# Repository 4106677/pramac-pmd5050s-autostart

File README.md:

# Pramac PMD5050S — автозапуск на ESP32 (ESPHome)

Заміна штатного блоку автозапуску (ATS) для дизель-генератора **Pramac PMD5050S** (двигун 186FA, 50 Гц ≈ 3000 об/хв): плата-носій на KiCad + прошивка ESPHome + картка Home Assistant.

> ⚠️ Це реальний генератор зі стартером і мережева напруга 230 В на виході контактора. Безпека важливіша за швидкість. Проєкт особистий, без гарантій; використовуєте на свій ризик.

| Плата, верх | Плата, низ | Home Assistant |
|---|---|---|
|  |  |  |

## Що вміє
- **Автозапуск** по сухому контакту REMOTE (інвертор/ATS) або перемикачу «Запуск з HA»: подає ACC, крутить стартер до появи обертів (до 3 спроб), тримає ACC, поки запит активний.
- **Контактор з прогрівом:** після запуску чекає **40 с**, потім замикає реле K3 (сухі COM/NO під котушку контактора 230 В). На **СТОП** спершу розмикає K3, двигун ще **20 с** працює без навантаження, потім знімається ACC. Несподівана зупинка двигуна одразу розмикає K3. Час задається `warmup_s`, `cooldown_s`.
- **Оберти** з сигналу TAHO (допоміжна обмотка маховика) через LM393: ~18 300 імп/хв ≈ 3 050 об/хв при 6 імп/оберт. Поріг «двигун працює» 1000 об/хв.
- **Моточаси** (`duty_time`, зберігаються у флеші, старт з нуля), логування обертів лише коли вони ≠ 0.
- **Безпечні стани:** після перезавантаження плати всі реле вимкнені (NPN-драйвер з підтяжкою бази до GND), запит з HA скидається, двигун сам не стартує.

## Плата v5.1 (KiCad 10, 93,2 × 82 мм, 2 шари)
Файли в [`hardware/`](hardware/):

| Файл | Призначення |
|---|---|
| `pramac_carrier.kicad_pcb` | плата (відкривається в KiCad PCB Editor) |
| `pramac_carrier_gerbers.zip` | Gerber + drill для виробника |
| `fit_check_1to1.pdf` | креслення 1:1, роздрукувати без масштабу й приміряти ESP32 та клеми |
| `BOM.md` | повний список компонентів |
| `pramac_carrier.kicad_dru` | правило зазору 2,5 мм для мережевих ланцюгів контактора |
| `generate_board.py`, `qr.txt` | генератор плати через `pcbnew` |

### Що змінилось у v5.1
- **RM20S-050:** на v5 контур корпусу на шовкографії був намальований не з того боку, тому модуль легко поставити задом наперед. Розводка виводів не змінилась (1 +VIN, 2 GND, 3 +VOUT), але тепер контур стоїть з боку D2, а біля виводів підписано **IN / GND / OUT**. На платі v5 модуль ставиться так само: корпусом до D2.
- **Іоністор SC1** (JEC 1 Ф 5,5 В, овал 16 × 8 × 14 мм) має власне посадкове місце з кроком 11,8 мм між ESP32 і реле K1/K2. Тепер він стоїть прямо на платі, без друкованої підставки.
- Щоб звільнити місце, ESP32 піднято на 2 мм, а шину +12 В до реле опущено й звужено до 4 мм.
- D1 і D2 зсунуто ліворуч, щоб звільнити місце під корпус RM20S. D3 перенесено під кріпильний отвір H1, F1 стоїть під D3, QR-код на звороті трохи нижче.

### Клеми (DG128-5.0, всі з одного боку)
`BATT−  BATT+` | `CHG+  CHG−` (зарядний паралельно входу, до запобіжника) | `ACC  START` (виходи реле NO, +12 В) | `CONTACTOR` (сухі COM/NO реле K3, 230 В) | `TAHO  REMOTE` (REMOTE — два контакти сухого контакту).

### Живлення і реле
- Запобіжник T 2 А (радіальний KLS5-102-5RT-020H) → TVS → 1N5821 → C1/C2 (2× 4700 мкФ) → DC-DC Favotek RM20S-050 (5 В 2 А) → 1N5821 → вузол 5 В (+ іоністор SC1).
- Реле: 3× SRD-05VDC-SL-A. K1 (ACC), K2 (START): COM до +12 В шиною 4 мм, NO на клему доріжкою 4 мм (≈10 А при 2 oz). Шина +12 В йде **до** запобіжника, тому на проводі від АКБ потрібен окремий зовнішній запобіжник (~15 А).
- Драйвер кожного реле: BC337 + резистор бази 1 кОм + підтяжка бази 10 кОм до GND + діод 1N4148 на котушці.

### ESP32
DevKit V1 30-pin **лежить горизонтально** (антена ліворуч, USB праворуч), вставляється в прямі гнізда 1×15 (відстань між рядами 25,4 мм). Під антеною немає міді, під модулем стоять лише низькі деталі.

| Пін | Призначення |
|---|---|
| D14 | TAHO (вихід LM393 → `pulse_counter`) |
| D25 | REMOTE, `INPUT_PULLUP`, замкнуто = GND (через R6 1 кОм, фільтр C6) |
| D2 / D4 / D26 | реле ACC / START / контактор (активний HIGH) |
| D27, D13 | резервний роз'єм J3 (не використовується в прошивці) |

### Вхід TAHO
Taho → R1 22 кОм → два стабілітрони BZX55C5V1 зустрічно на GND → C3 10 мкФ (неполярний) → LM393 IN−; зсув 1,65 В дільником 10 кОм/10 кОм, гістерезис R4 100 кОм, pull-up R5 4,7 кОм на 3V3. Живий дріт Taho **не можна** садити на масу.

### Нижній бік
QR на цей репозиторій, логотип GitHub і нік.

## Прошивка
```bash
cd esphome
cp secrets.yaml.example secrets.yaml   # заповніть своїми значеннями
esphome config pramac-pmd5050s.yaml
esphome compile pramac-pmd5050s.yaml
```
ESPHome 2025.4.1. Константи: `pulses_per_rev`, `running_rpm_threshold`, `warmup_s`, `cooldown_s` у `substitutions`. Для цієї плати реле мають `inverted: false`.

## Home Assistant
Картка зі шкалою обертів і перемикачем: [`homeassistant/generator-card.yaml`](homeassistant/generator-card.yaml) (замініть entity_id на свої; для перемикача «Запуск з HA» варто увімкнути підтвердження натискання).

## Корпус для друку (ABS)
Основа + кришка + червона вставка з логотипом Pramac (без гвинтів, на клею), додаткові опори й напрямні для плати, кріплення на стіну вушками, кришка на M3 з латунними вставками. Параметрична модель: [`enclosure/`](enclosure/) (STL, скрипт для Fusion, генератор на Python, інструкція).

## Замовлення плати
Для PCBWay: 2 шари, 1,6 мм, мідь **2 oz** (шина 10 А), HASL без свинцю, файл `pramac_carrier_gerbers.zip`. Майже всі компоненти виводні (THT), тож плату зручно паяти вручну; готові модулі (ESP32 DevKit, RM20S) ставляться як є.

## Порядок першого запуску
1. Роздрукувати `fit_check_1to1.pdf` 1:1, приміряти ESP32, колодки, клеми (відстань між рядами, висота під модулем ~8,5 мм).
2. Зібрати плату без ESP32, перевірити 5 В і 3,3 В, TVS/запобіжник.
3. Прошити, перевірити, що **всі три реле вимкнені** при подачі живлення й після кількох перезавантажень.
4. Перевірити TAHO на працюючому двигуні (~3 050 об/хв), звірити `pulses_per_rev` (частота на виході × 60).
5. Дріт **START до генератора підключати останнім**.
6. Контактор перевірити окремо без навантаження (прогрів 40 с, СТОП: K3 розмикається, через 20 с знімається ACC).

## Жорсткі правила
- START підключати останнім, після перевірки, що реле вимкнені під час завантаження.
- Не додавати логіку, яка вмикає START, коли двигун міг уже крутитися.
- Знятий ACC = двигун глухне; реле ACC вимикається при перезавантаженні плати (свідомий компроміс).
- Захист TAHO не послаблювати без обговорення.
- Мережеві (230 В) ланцюги контактора перевіряти окремо: плата не сертифікована.

## Відкрите
- Звірити `pulses_per_rev` по частоті на виході генератора.
- Не перевірено на залізі: відстань між рядами ESP32, розпіновка D-підписів вашого DevKit, розпіновка клемників (за datasheet), зазори мережевого ланцюга.
- Brownout під час старту Wi-Fi: перевірити 5 В на VIN ESP32.
- Схеми `.kicad_sch` немає: плата зібрана з нетлисту в скрипті.
- Рівень пального: пізніше.

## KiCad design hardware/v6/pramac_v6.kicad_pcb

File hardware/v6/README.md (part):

# Плата v6.1

**v6.1 (14.11.2026): переробка входу TAHO.** Перевірено на платі 5.1 з тією самою схемою входу:
у v6.0 резистор R31 тягнув вхід LM393 до опорної напруги VB, і в спокої компаратор стояв на порозі та ловив шум
(оберти росли до 20 000 на заглушеному двигуні). Тепер:
- **R31 10k** іде з TAHO_AC на GND: у спокої вхід на 0 В, нижче порогу, вихід LM393 HIGH.
- **Поріг VB:** R32 22k / R33 10k + гістерезис R34 100k дають 0,97 / 1,18 В (на 5.1 після переробки виміряно 1,2 В).
- **Фільтр R38 10k / C33 10 нФ** (100 мкс) перед LM393 гасить короткі (3–25 мкс) голки від регулятора зарядки генератора.
- **BAV99 (D25)** обмежує вхід LM393 від −0,6 до ~3,9 В.

Решта плати без змін: розводку v6.0 збережено, заново розведені тільки ланцюги TAHO_AC, TAHO_F і VB
(`patch_v61.py prep <плата v6.0>` → Freerouting → `patch_v61.py finish` → `gen_pcb.py export`).
DRC: 0 помилок, 0 незведених, 3 попередження про шовкографію (ті самі, що у v6.0).
Прошивка для v6 ще не написана; рахувати оберти треба так само, як `esphome/taho_rpm.h` (полярність входу та сама, що на переробленій 5.1).

Плата під заводську збірку JLCPCB (PCBA): майже все SMD, решту (реле, клеми, модуль AC-DC, мережевий запобіжник, варистор) завод теж паяє, сервісом THT. Допаювати нічого не треба.

| Файл | Що це |
|---|---|
| `pramac_v6_schematic.pdf` | схема для перегляду |
| `pramac_v6.kicad_sch`, `pramac_v6.kicad_pro`, `pramac_v6.kicad_sym`, `sym-lib-table` | проєкт KiCad 10 (схема + власні символи CN3767 і AO4421) |
| `pramac_v6_bom.csv` | BOM у форматі JLCPCB (Comment, Designator, Footprint, LCSC) |
| `gen_schematic.py`, `charger.py`, `parts.py`, `kisch.py` | генератор схеми: `python3 gen_schematic.py` |
| `pramac_v6.kicad_pcb`, `pramac_v6.kicad_dru` | плата 125 × 100 мм, 2 шари, і правило зазору 2,5 мм для 230 В |
| `pramac_v6_gerbers.zip` | гербери + свердління для JLCPCB |
| `pramac_v6_bom.csv`, `pramac_v6_cpl.csv` | BOM і файл розміщення (CPL) для заводської збірки |
| `pcb-top.png`, `pcb-bottom.png`, `drc.rpt` | рендери і звіт DRC |
| `gen_pcb.py`, `pramac_v6.dsn`, `pramac_v6.ses` | генератор плати: `gen_pcb.py place` → Freerouting (`.dsn` → `.ses`) → `gen_pcb.py route` → `gen_pcb.py export` |

## Що змінилось порівняно з v5.1
- **ESP32-S3-MINI-1U-N8** розпаяний на платі (15,4 × 15,4 мм), роз'єм U.FL під зовнішню антену: кабель U.FL → SMA на стінці корпусу. Прошивка й лог по USB-C (USB вбудований у чип), кнопки BOOT і RESET.
- **Живлення без іоністора:** два маленькі перетворювачі прямо від АКБ. AP63203 дає 3,3 В для ESP32 і працює від 3,8 В. AP63205 дає окремі 5 В для котушок реле. Обидва мають режим LDO: коли АКБ під час прокрутки падає нижче 5 В, вихід 5 В іде слідом за входом, а реле SRD-05 тримаються аж до ~2 В на котушці. Тому **іоністор більше не потрібен**.
- **Реле** ті самі Songle SRD-05VDC-SL-C. Ключі AO3400A, діоди на котушках, світлодіод стану на кожному реле.
- **Четверте реле K4 AUX** для підігрівача перед пуском або соленоїда декомпресії. COM на шині АКБ, як у ACC і START, вихід на окремий клемник J8 (AUX, GND).
- **Зарядка АКБ від 230 В:** модуль Mean Well IRM-20-24 → зарядник CN3767. Заряд 14,8 В, підтримка 13,55 В (задані всередині мікросхеми), струм 1 А. Підходить для звичайних свинцевих і AGM.
- **Детектор мережі:** оптопара LTV-814 на вході 230 В.
- **DIP-перемикач на 4 позиції** для вибору режиму, **4 кріплення M3 по кутах**, знімні клемники 5,08 мм.

## Живлення
`BATTERY+` → самовідновлюваний запобіжник 2 А (PTC) → `VBF` (TVS SMBJ18A, вихід зарядника, вимір напруги АКБ) → SS54 → `VIN12` (470 мкФ).
Від `VIN12` живляться AP63203 (3,3 В, ESP32) і AP63205 (`V5`, тільки котушки реле й світлодіоди реле).
Від USB: `VBUS` → SS34 → `VIN12`, тобто ESP32 можна прошити без 12 В.
Шина `VBAT` (до запобіжника) іде на COM реле ACC і START. На дроті від АКБ, як і раніше, потрібен зовнішній запобіжник ~15 А.

## Зарядник
- **Живлення і перемикач:** `V24` з модуля через P-MOSFET Q20. Ним керує ESP32 (`CHG_EN`): HIGH, або коли ESP32 не працює, зарядка йде; LOW — вимкнена. Прошивка вимикає зарядку на час прокрутки стартера і коли DIP2 вимкнений.
- **Струм:** 0,12 В / R66 = 1 А при R66 = 0,12 Ом. Модуль на 20 Вт має запас: зарядник бере близько 17 Вт.
- **Захист модуля від перевантаження:** дільник MPPT (150k/10k). Якщо модуль просяде нижче ~19 В, зарядник сам зменшить струм.
- **Стан:** `CHG_STAT` (заряджається) і `CHG_DONE` (заряджено) йдуть на ESP32 і на два світлодіоди.

## Піни ESP32-S3
| GPIO | Сигнал | GPIO | Сигнал |
|---|---|---|---|
| IO1 | напруга АКБ (АЦП, дільник 100k/22k) | IO9 | світлодіод STATUS |
| IO2 | CHG_DONE | IO10 / IO11 / IO12 | реле K1 ACC / K2 START / K3 контактор |
| | | IO21 | реле K4 AUX |
| IO4 | TAHO (LM393) | IO13–IO16 | DIP1–DIP4 |
| IO5 | REMOTE (сухий контакт між двома клемами REMOTE) | IO17, IO18 | резервна гребінка J7 |
| IO6 | MAINS_OK (мережа є = LOW) | IO19 / IO20 | USB D− / D+ |
| IO7 | CHG_EN | IO0 / EN | BOOT / RESET |
| IO8 | CHG_STAT | | |

## DIP-перемикач
1. Режим: OFF — запуск за сигналом REMOTE; ON — запуск, коли пропала мережа.
2. Зарядка дозволена.
3. Затримка запуску: 10 с або 60 с.
4. AUX: OFF — K4 працює як підігрів (вмикається на N секунд до прокрутки), ON — як декомпресія (тримається під час прокрутки).

## Роз'єми (знімні клемники 5,08 мм)
| Роз'єм | Контакти |
|---|---|
| J1 | AC IN: L, N |
| J2 | CONTACTOR: COM, NO (сухі контакти, 230 В) |
| J3 | BATTERY: +, − |
| J4 | ACC, START |
| J5 | TAHO; REMOTE, REMOTE (два контакти під сухий контакт або кнопку, полярність не важлива) |
| J8 | AUX: вихід K4 (+12 В з АКБ), GND |

Плагіни до клемників (WJ2EDGK, 5 × 2P і 1 × 3P) JLCPCB надсилає разом із замовленням окремими деталями.

**Навантаження на AUX.** Контакт реле SRD розрахований на 10 А. Свічки розжарювання і соленоїд декомпресії в момент втягування часто беруть більше. Тому для них ставте зовнішнє автомобільне реле на 30–40 А: його котушку підключити до J8 (AUX і GND), а силові контакти — напряму від АКБ через свій запобіжник. Слабке навантаження до ~8 А можна живити від J8 напряму.

## Плата
- **Розмір і кріплення:** 125 × 100 мм, 2 шари, 4 отвори M3 по кутах (за 4 мм від країв).
- **Зона 230 В ліворуч:** модуль AC-DC, запобіжник, варистор, реле контактора K3, детектор мережі (три резистори й оптопара під модулем AC-DC), клемники AC IN і CONTACTOR. Полігону землі там немає. Правило DRC тримає ≥ 2,5 мм від будь-якої мережевої міді до низьковольтної. Оптопара й модуль AC-DC стоять на межі зон.
- **Реле K4, K1, K2** стоять в один ряд на місці, що звільнилось у нижньому лівому куті. Їхні COM з'єднує одна шина АКБ.
- **Сильнострумові ланцюги** розведені вручну по нижньому шару. Шина АКБ від J3 до COM реле і виходи ACC/START/AUX мають ширину 3–4 мм.
- **Решта** розведена Freerouting. Земля: полігони з обох боків, перехідні отвори біля кожного SMD-виводу GND і зшивання сіткою 5 мм.
- **DRC:** 0 помилок, усі зв'язки з'єднані. Лишилось 3 попередження про шовкографію; на виводах завод її сам обрізає.
- **Розташування:** ESP32 угорі праворуч (роз'єм U.FL для кабелю до SMA на корпусі), USB-C на правому краю, кнопки RESET/BOOT під модулем, клемники вздовж нижнього краю.

## Замовлення на JLCPCB
- **PCB:** 2 шари, 1,6 мм, мідь **2 oz** (струм реле до 10 А), HASL без свинцю, файл `pramac_v6_gerbers.zip`.
- **Збірка:** у PCB Assembly завантажити `pramac_v6_bom.csv` і `pramac_v6_cpl.csv`. Виводні деталі (реле, клемники, IRM-20-24, запобіжник, варистор) завод теж паяє, сервісом THT.
- **Обов'язково перегляньте в превʼю JLCPCB поворот деталей:** у бібліотеки JLC своя орієнтація, і частину кутів (SOT-23, діоди, модуль ESP32, USB-C) зазвичай доводиться підправити там же.
- **Звірте посадкові місця на етапі DFM JLCPCB.** Їх я взяв з бібліотеки KiCad, вони відповідають корпусам у даташитах, але завод це перевіряє окремо:
  - клемники WJ2EDGRC (посадкове місце Phoenix MSTBA 5,08);
  - оптопара LTV-814S (SMDIP-4);
  - DIP-перемикач.
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
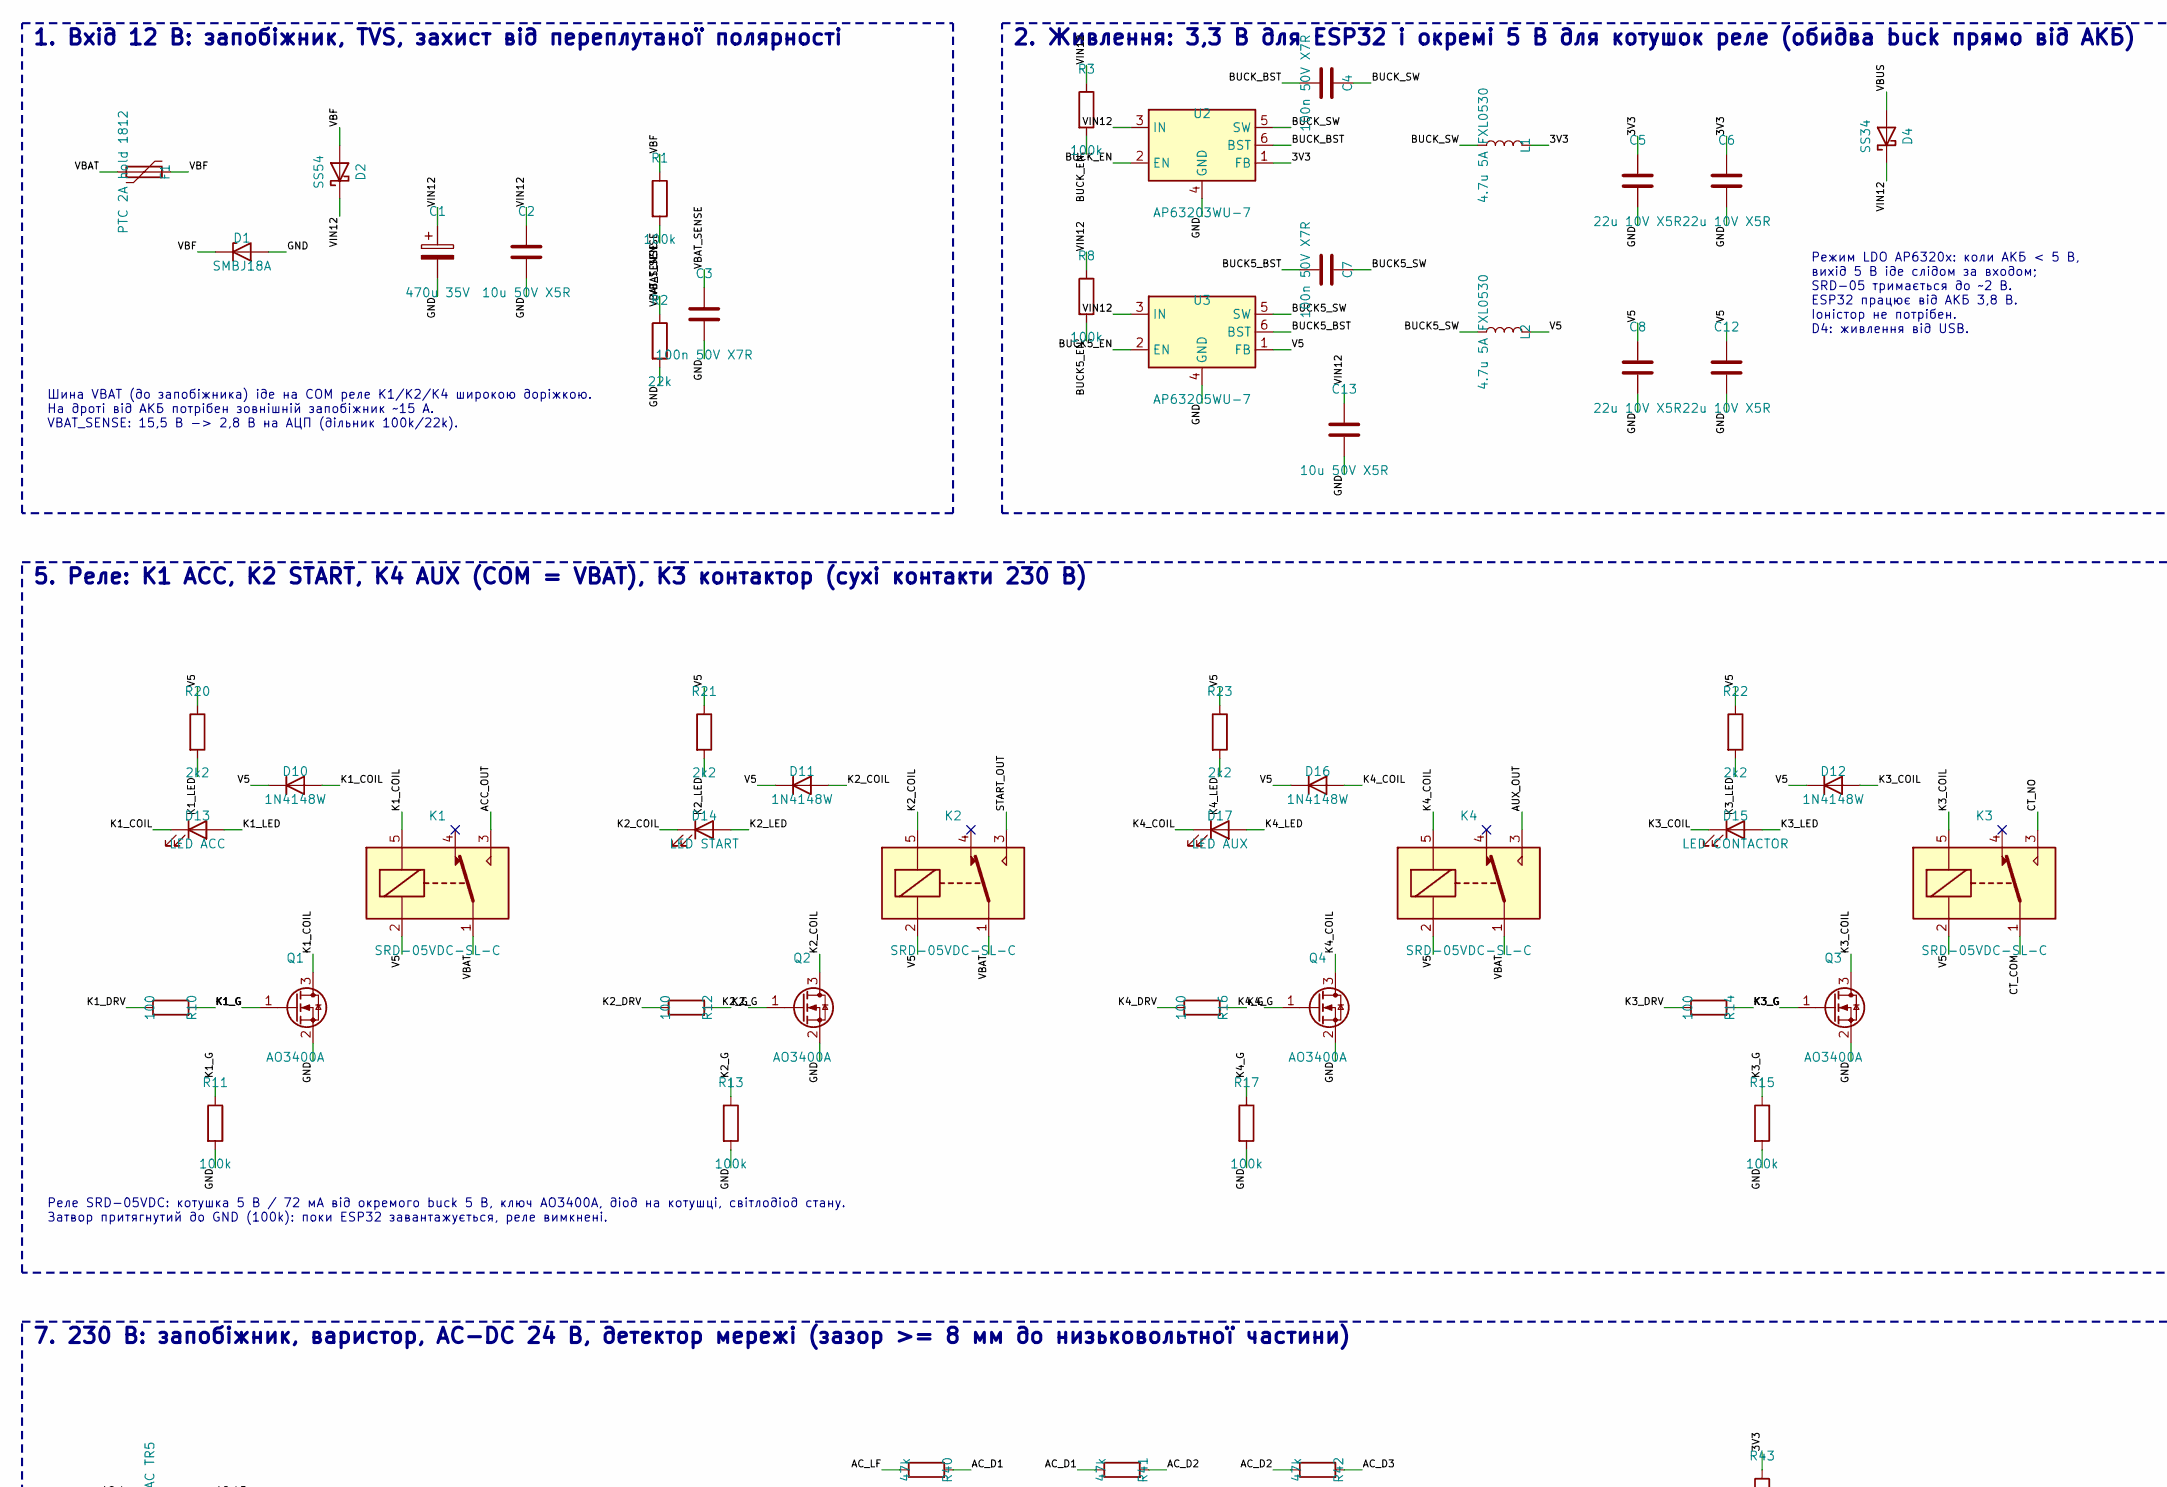
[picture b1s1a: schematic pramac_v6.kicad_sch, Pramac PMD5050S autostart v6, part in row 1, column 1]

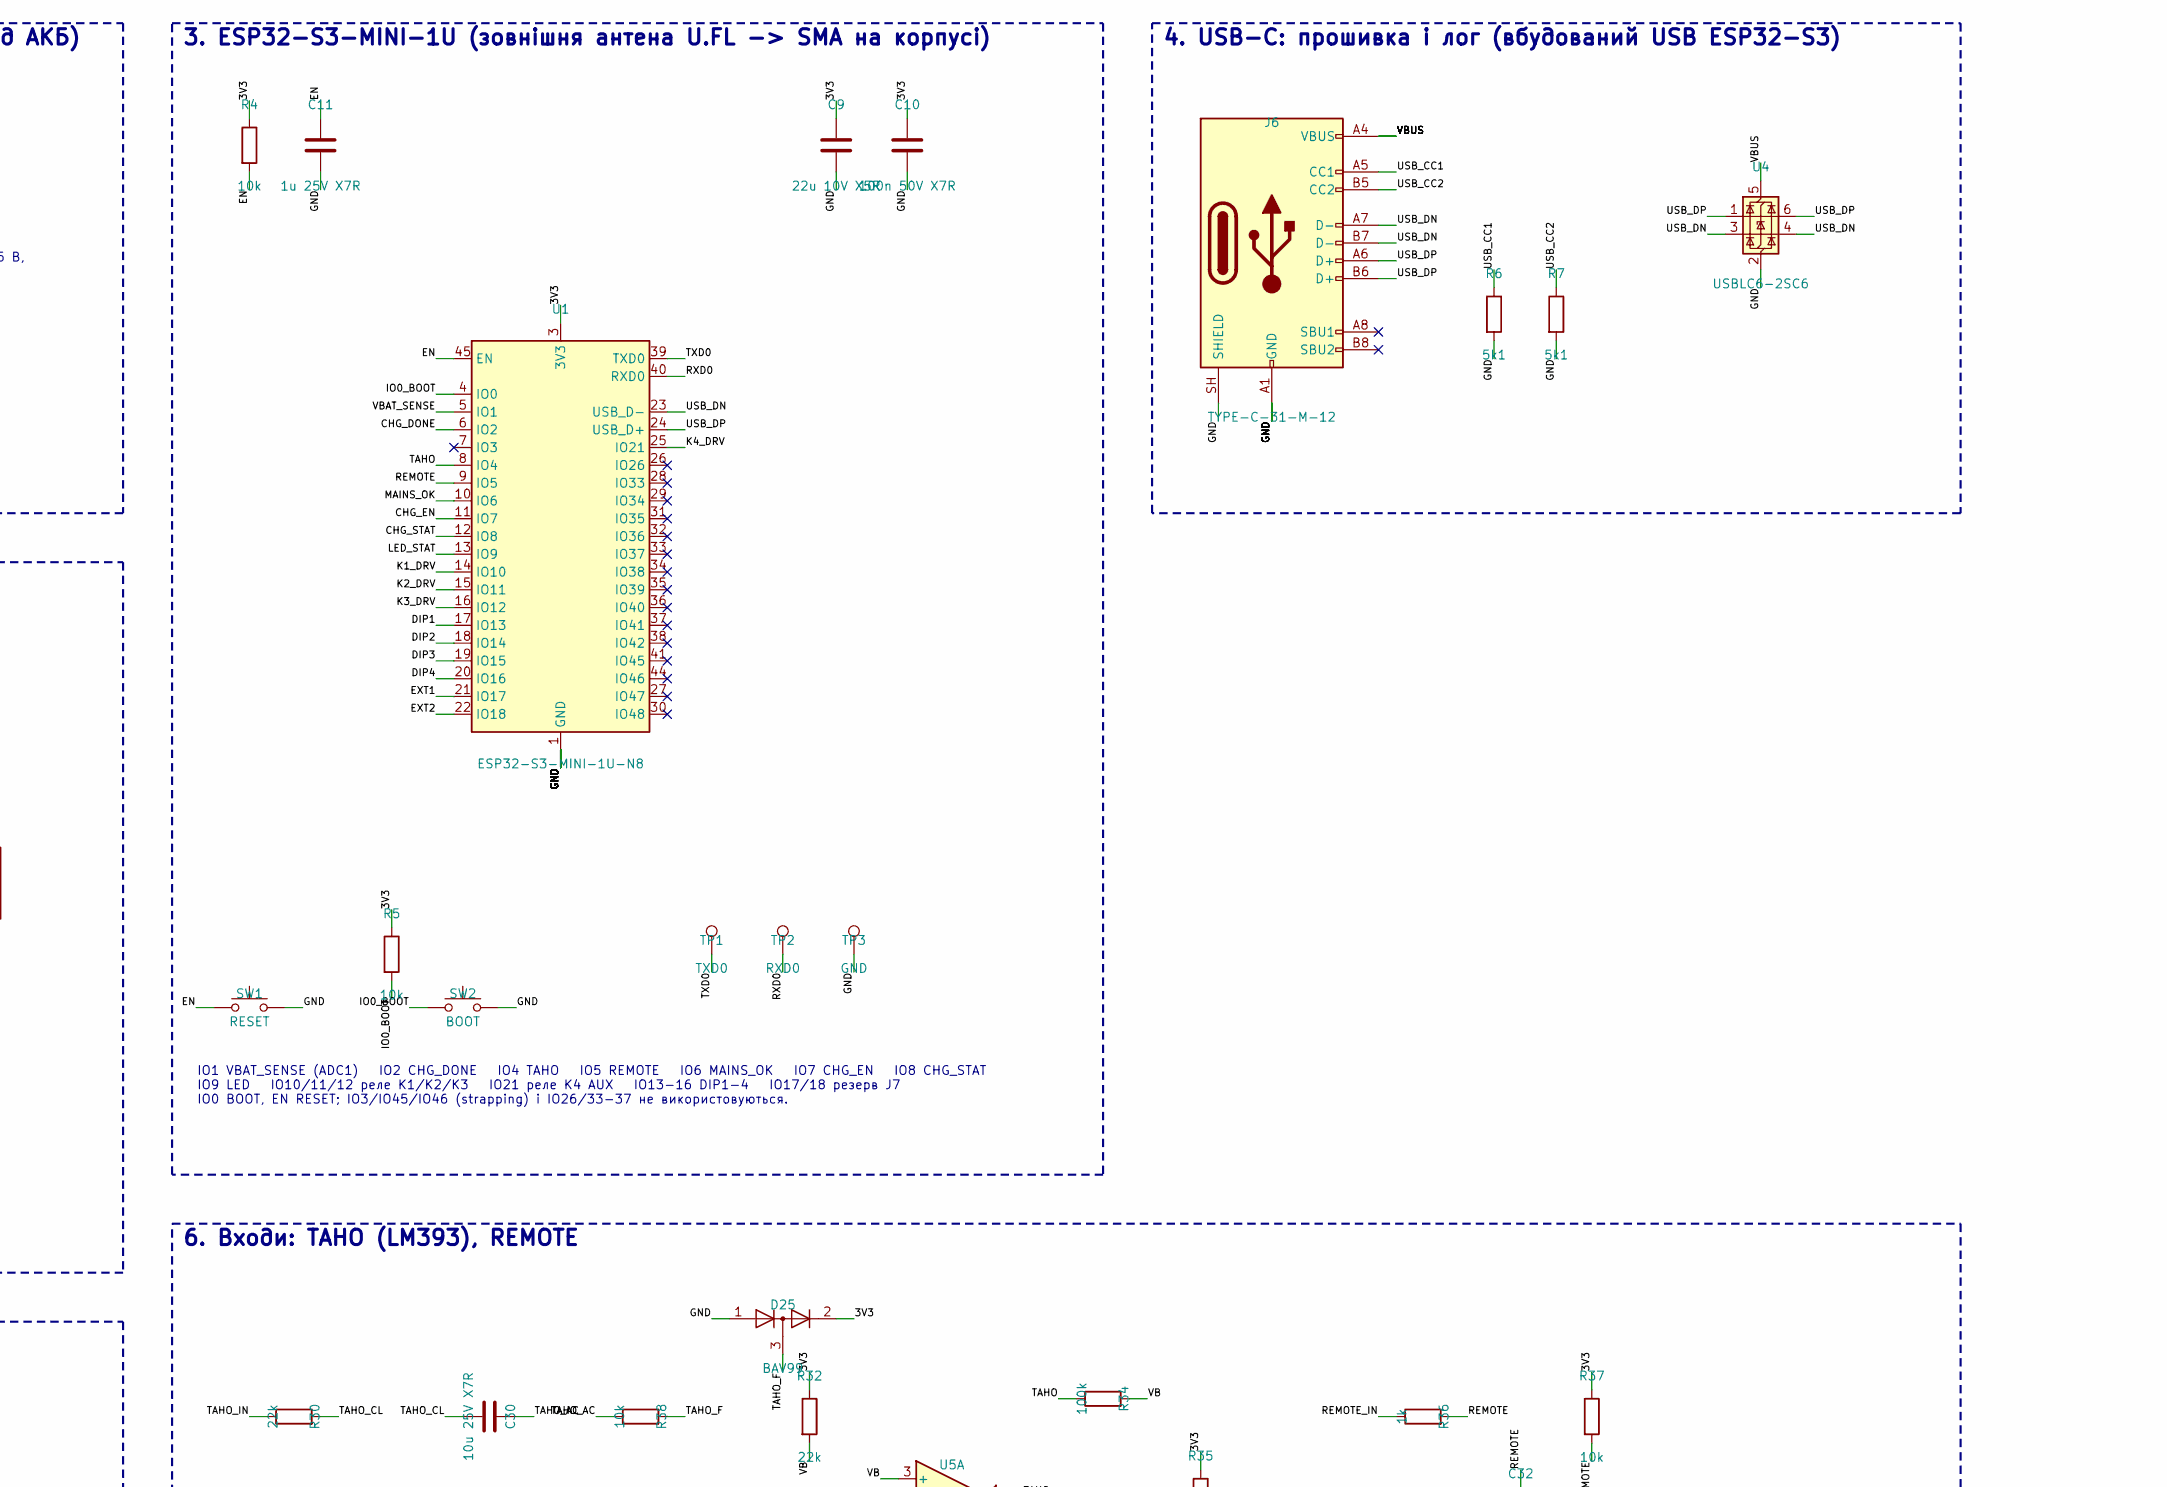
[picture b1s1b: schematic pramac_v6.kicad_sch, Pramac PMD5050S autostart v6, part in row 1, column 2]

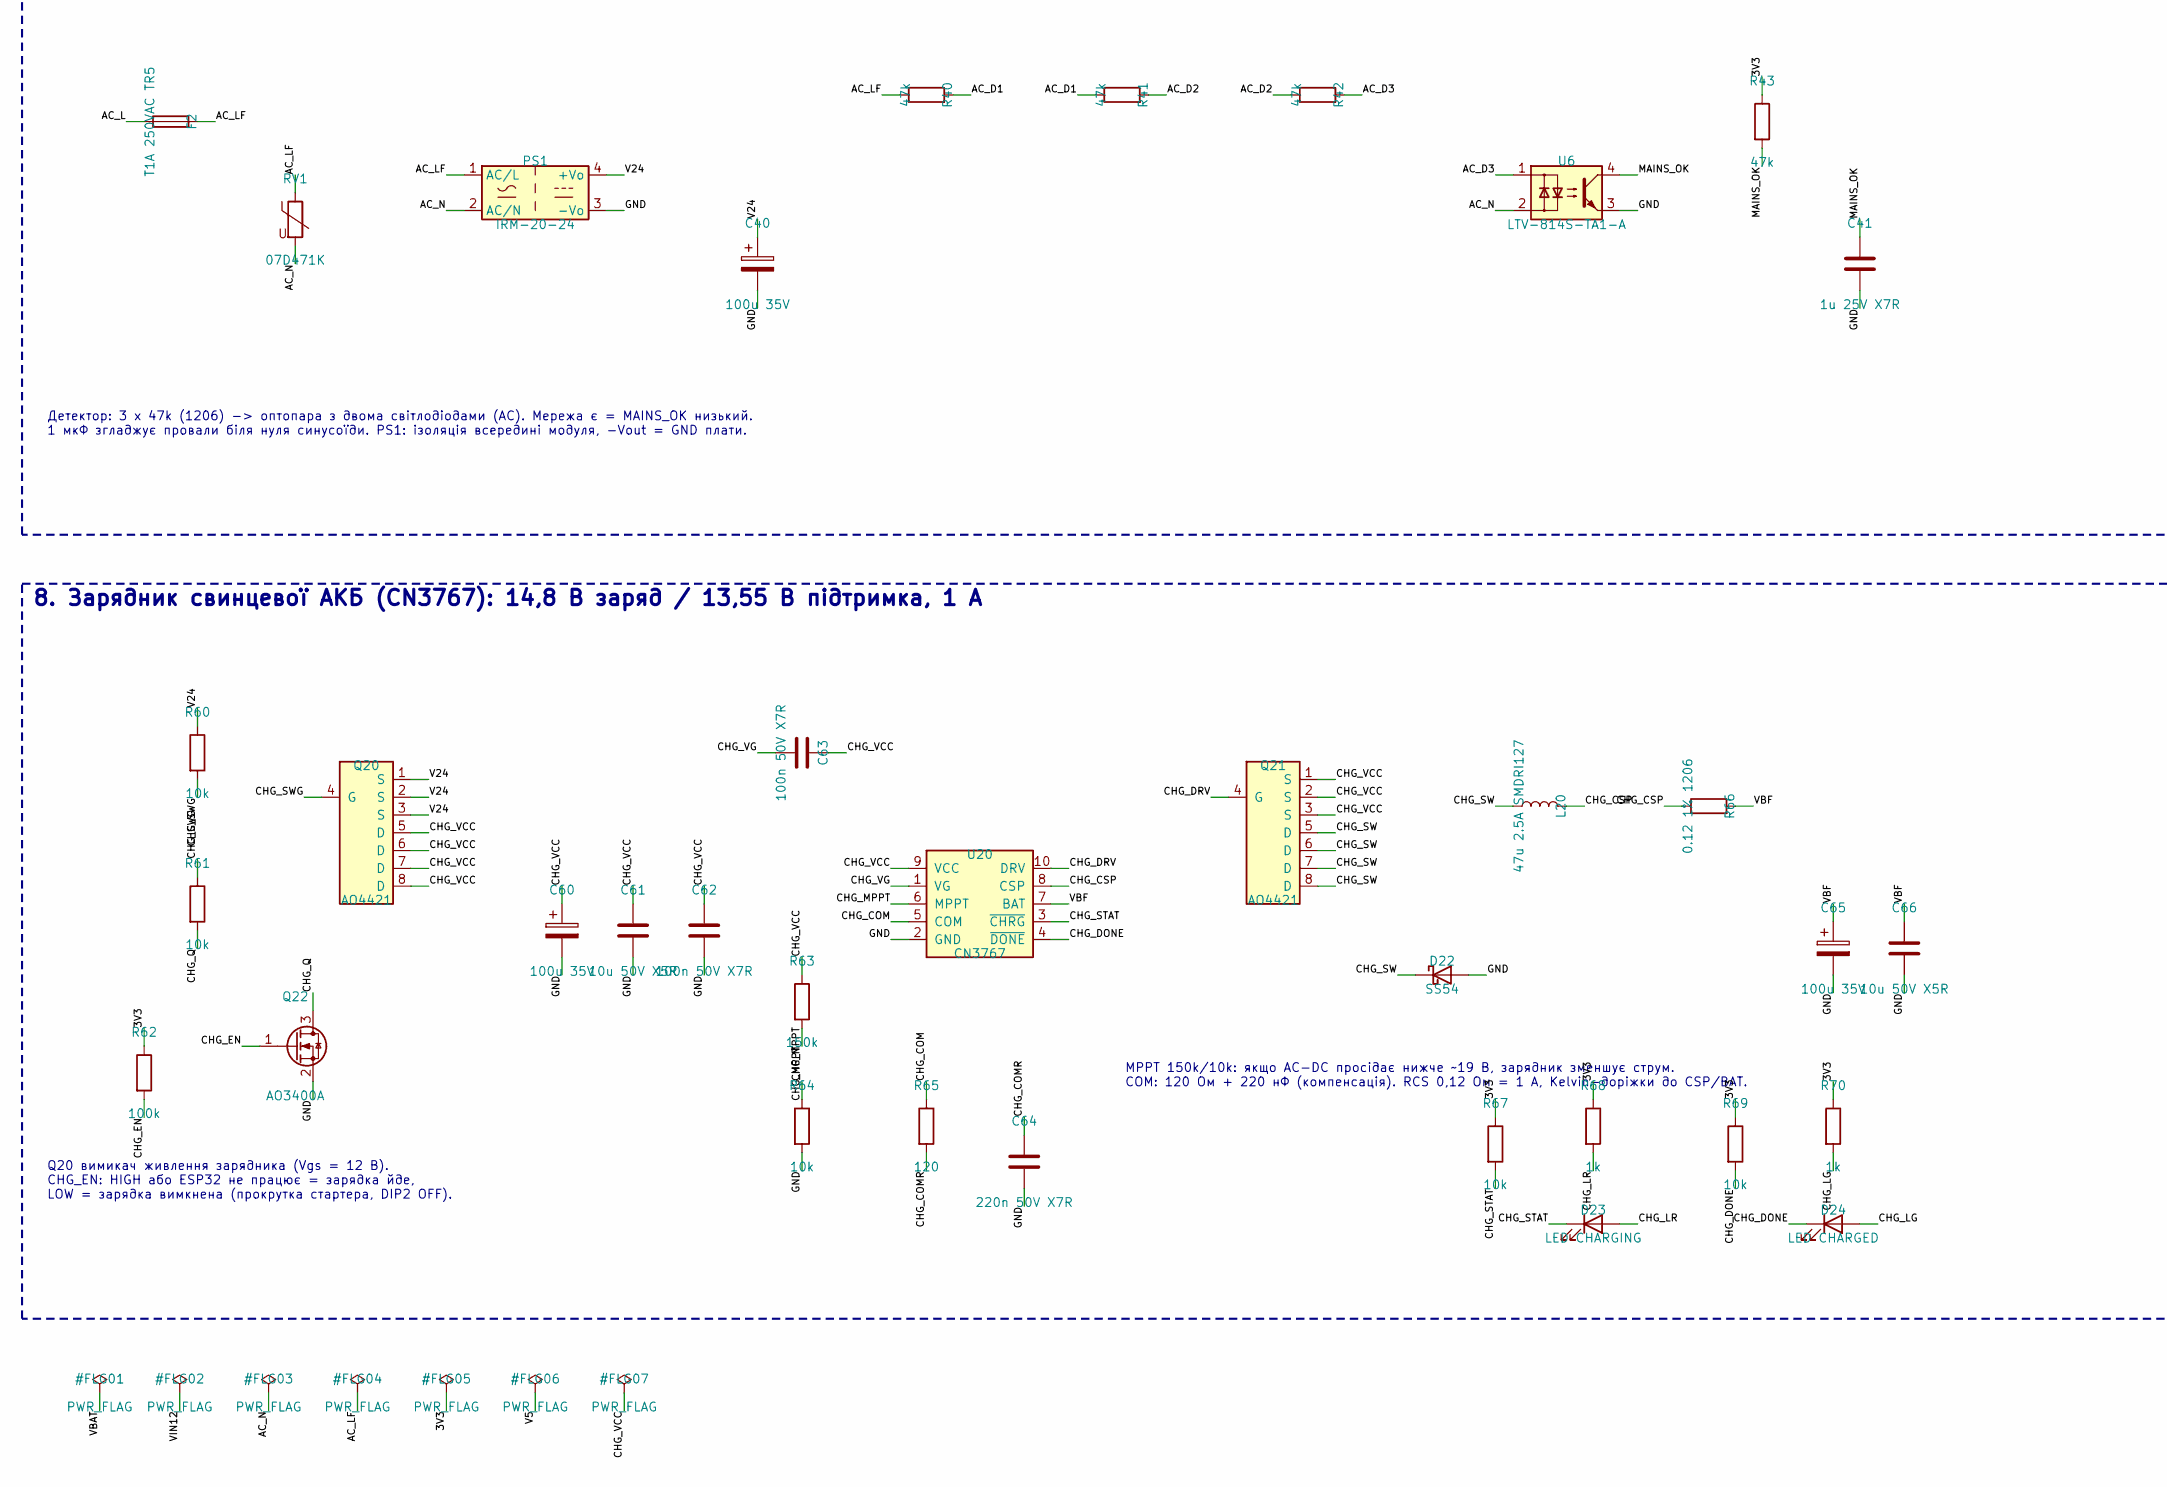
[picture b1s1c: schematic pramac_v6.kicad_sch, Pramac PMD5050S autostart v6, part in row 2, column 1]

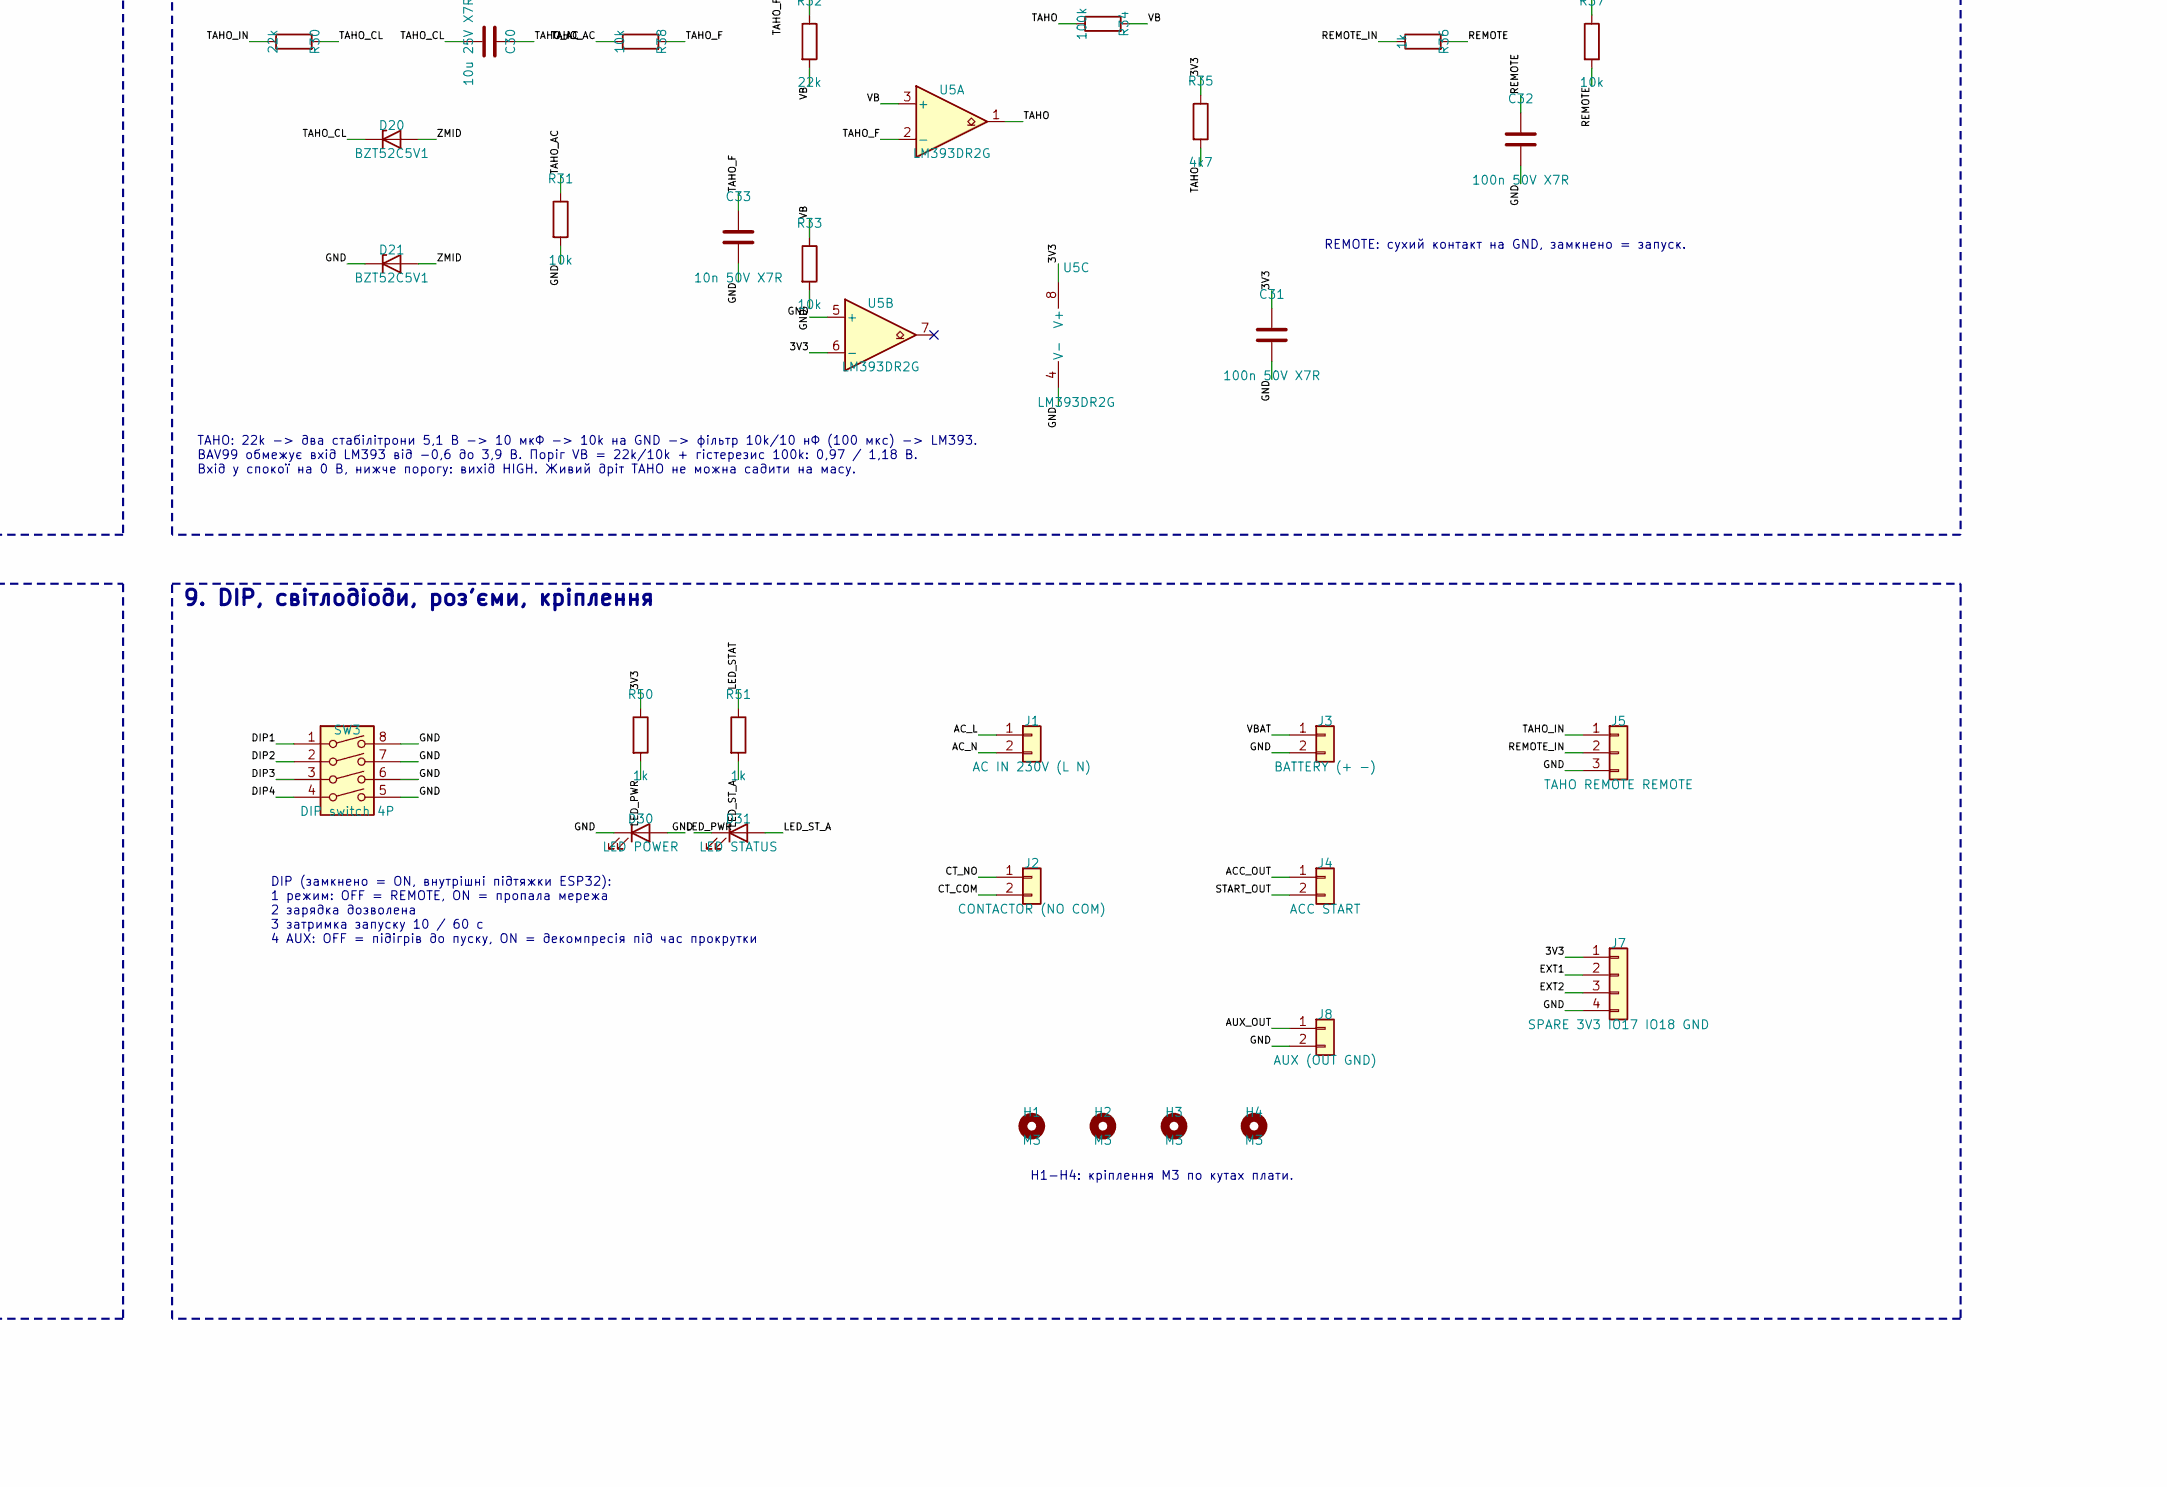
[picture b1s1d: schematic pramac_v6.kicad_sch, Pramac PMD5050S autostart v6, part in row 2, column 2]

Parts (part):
C1: 470u 35V; CP_Elec_10x10.5; LCSC C2836436
C2, C13, C61, C66: 10u 50V X5R; C_1206_3216Metric; LCSC C13585
C3, C4, C7, C10, C31, C32, C62, C63: 100n 50V X7R; C_0805_2012Metric; LCSC C49678
C5, C6, C8, C9, C12: 22u 10V X5R; C_0805_2012Metric; LCSC C380338
C11, C41: 1u 25V X7R; C_0805_2012Metric; LCSC C89190
C30: 10u 25V X7R; C_1206_3216Metric; LCSC C70462
C33: 10n 50V X7R; C_0805_2012Metric; LCSC C1710
C40, C60, C65: 100u 35V; CP_Elec_6.3x7.7; LCSC C2836442
C64: 220n 50V X7R; C_0805_2012Metric; LCSC C5378
D1: SMBJ18A; D_SMB; LCSC C353379
D2, D22: SS54; D_SMA; LCSC C22452
D4: SS34; D_SMA; LCSC C8678
D10, D11, D12, D16: 1N4148W; D_SOD-123; LCSC C81598
D13: LED ACC; LED_0805_2012Metric; LCSC C84256
D14: LED START; LED_0805_2012Metric; LCSC C84256
D15: LED CONTACTOR; LED_0805_2012Metric; LCSC C84256
D17: LED AUX; LED_0805_2012Metric; LCSC C84256
D20, D21: BZT52C5V1; D_SOD-123; LCSC C2117
D23: LED CHARGING; LED_0805_2012Metric; LCSC C84256
D24: LED CHARGED; LED_0805_2012Metric; LCSC C2297
D25: BAV99; SOT-23; LCSC C2500
D30: LED POWER; LED_0805_2012Metric; LCSC C2297
D31: LED STATUS; LED_0805_2012Metric; LCSC C2297
F1: PTC 2A hold 1812; Fuse_1812_4532Metric; LCSC C434887
F2: T1A 250VAC TR5; Fuse_Littelfuse_372_D8.50mm; LCSC C142808
H1, H2, H3, H4: M3; MountingHole_3.2mm_M3
J1: AC IN 230V (L N); PhoenixContact_MSTBA_2,5_2-G-5,08_1x02_P5.08mm_Horizontal; LCSC C3697
J2: CONTACTOR (NO COM); PhoenixContact_MSTBA_2,5_2-G-5,08_1x02_P5.08mm_Horizontal; LCSC C3697
J3: BATTERY (+ -); PhoenixContact_MSTBA_2,5_2-G-5,08_1x02_P5.08mm_Horizontal; LCSC C3697
J4: ACC START; PhoenixContact_MSTBA_2,5_2-G-5,08_1x02_P5.08mm_Horizontal; LCSC C3697
J5: TAHO REMOTE REMOTE; PhoenixContact_MSTBA_2,5_3-G-5,08_1x03_P5.08mm_Horizontal; LCSC C8377
J6: TYPE-C-31-M-12; USB_C_Receptacle_HRO_TYPE-C-31-M-12; LCSC C165948
J7: SPARE 3V3 IO17 IO18 GND; PinHeader_1x04_P2.54mm_Vertical; LCSC C2691448
J8: AUX (OUT GND); PhoenixContact_MSTBA_2,5_2-G-5,08_1x02_P5.08mm_Horizontal; LCSC C3697
K1, K2, K3, K4: SRD-05VDC-SL-C; Relay_SPDT_SANYOU_SRD_Series_Form_C; LCSC C35449
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
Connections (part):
3V3: C5.1, C6.1, C9.1, C10.1, C31.1, D25.2 (A), J7.1, L1.2, R4.1, R5.1, R32.1, R35.1, R37.1, R43.1, R50.1, R62.1, R67.1, R68.1, R69.1, R70.1, U1.3 (3V3), U2.1 (FB), U5.6 (-), U5.8 (V+)
ACC_OUT: J4.1, K1.3
AC_D1: R40.2, R41.1
AC_D2: R41.2, R42.1
AC_D3: R42.2, U6.1
AC_L: F2.1, J1.1
AC_LF: F2.2, PS1.1 (AC/L), R40.1, RV1.1
AC_N: J1.2, PS1.2 (AC/N), RV1.2, U6.2
AUX_OUT: J8.1, K4.3
BUCK5_BST: C7.1, U3.6 (BST)
BUCK5_EN: R8.2, U3.2 (EN)
BUCK5_SW: C7.2, L2.1, U3.5 (SW)
BUCK_BST: C4.1, U2.6 (BST)
BUCK_EN: R3.2, U2.2 (EN)
BUCK_SW: C4.2, L1.1, U2.5 (SW)
CHG_COM: R65.1, U20.5 (COM)
CHG_COMR: C64.1, R65.2
CHG_CSP: L20.2, R66.1, U20.8 (CSP)
CHG_DONE: D24.1 (K), R69.2, U1.6 (IO2), U20.4 (~DONE)
CHG_DRV: Q21.4 (G), U20.10 (DRV)
CHG_EN: Q22.1 (G), R62.2, U1.11 (IO7)
CHG_LG: D24.2 (A), R70.2
CHG_LR: D23.2 (A), R68.2
CHG_MPPT: R63.2, R64.1, U20.6 (MPPT)
CHG_Q: Q22.3 (D), R61.2
CHG_STAT: D23.1 (K), R67.2, U1.12 (IO8), U20.3 (~CHRG)
CHG_SW: D22.1 (K), L20.1, Q21.5 (D), Q21.6 (D), Q21.7 (D), Q21.8 (D)
CHG_SWG: Q20.4 (G), R60.2, R61.1
CHG_VCC: C60.1, C61.1, C62.1, C63.2, Q20.5 (D), Q20.6 (D), Q20.7 (D), Q20.8 (D), Q21.1 (S), Q21.2 (S), Q21.3 (S), R63.1, U20.9 (VCC)
CHG_VG: C63.1, U20.1 (VG)
CT_COM: J2.2, K3.1
CT_NO: J2.1, K3.3
DIP1: SW3.1, U1.17 (IO13)
DIP2: SW3.2, U1.18 (IO14)
DIP3: SW3.3, U1.19 (IO15)
DIP4: SW3.4, U1.20 (IO16)
EN: C11.1, R4.2, SW1.1, U1.45 (EN)
EXT1: J7.2, U1.21 (IO17)
EXT2: J7.3, U1.22 (IO18)
GND: C1.2, C2.2, C3.2, C5.2, C6.2, C8.2, C9.2, C10.2, C11.2, C12.2, C13.2, C31.2, C32.2, C33.2, C40.2, C41.2, C60.2, C61.2, C62.2, C64.2, C65.2, C66.2, D1.2 (A), D21.1 (K), D22.2 (A), D25.1 (K), D30.1 (K), D31.1 (K), J3.2, J5.3, J6.A1 (GND), J6.A12 (GND), J6.B1 (GND), J6.B12 (GND), J6.SH (SHIELD), J7.4, J8.2, PS1.3 (-Vo), Q1.2 (S), Q2.2 (S), Q3.2 (S), Q4.2 (S), Q22.2 (S), R2.2, R6.2, R7.2, R11.2, R13.2, R15.2, R17.2, R31.2, R33.2, R64.2, SW1.2, SW2.2, SW3.5, SW3.6, SW3.7, SW3.8, TP3.1, U1.1 (GND), U1.2 (GND), U1.42 (GND), U1.43 (GND), U1.46 (GND), U1.47 (GND), U1.48 (GND), U1.49 (GND), U1.50 (GND), U1.51 (GND), U1.52 (GND), U1.53 (GND), U1.54 (GND), U1.55 (GND), U1.56 (GND), U1.57 (GND), U1.58 (GND), U1.59 (GND), U1.60 (GND), U1.61 (GND)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
IO0_BOOT: R5.2, SW2.1, U1.4 (IO0)
K1_COIL: D10.2 (A), D13.1 (K), K1.5, Q1.3 (D)
K1_DRV: R10.1, U1.14 (IO10)
K1_G: Q1.1 (G), R10.2, R11.1
K1_LED: D13.2 (A), R20.2
K2_COIL: D11.2 (A), D14.1 (K), K2.5, Q2.3 (D)
K2_DRV: R12.1, U1.15 (IO11)
K2_G: Q2.1 (G), R12.2, R13.1
K2_LED: D14.2 (A), R21.2
K3_COIL: D12.2 (A), D15.1 (K), K3.5, Q3.3 (D)
K3_DRV: R14.1, U1.16 (IO12)
K3_G: Q3.1 (G), R14.2, R15.1
K3_LED: D15.2 (A), R22.2
K4_COIL: D16.2 (A), D17.1 (K), K4.5, Q4.3 (D)
K4_DRV: R16.1, U1.25 (IO21)
K4_G: Q4.1 (G), R16.2, R17.1
K4_LED: D17.2 (A), R23.2
LED_PWR: D30.2 (A), R50.2
LED_STAT: R51.1, U1.13 (IO9)
LED_ST_A: D31.2 (A), R51.2
MAINS_OK: C41.1, R43.2, U1.10 (IO6), U6.4
REMOTE: C32.1, R36.2, R37.2, U1.9 (IO5)
REMOTE_IN: J5.2, R36.1
RXD0: TP2.1, U1.40 (RXD0)
START_OUT: J4.2, K2.3
TAHO: R34.1, R35.2, U1.8 (IO4), U5.1
TAHO_AC: C30.2, R31.1, R38.1
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
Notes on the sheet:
1. Вхід 12 В: запобіжник, TVS, захист від переплутаної полярності
Шина VBAT (до запобіжника) іде на COM реле K1/K2/K4 широкою доріжкою. На дроті від АКБ потрібен зовнішній запобіжник ~15 А. VBAT_SENSE: 15,5 В -> 2,8 В на АЦП (дільник 100k/22k).
2. Живлення: 3,3 В для ESP32 і окремі 5 В для котушок реле (обидва buck прямо від АКБ)
Режим LDO AP6320x: коли АКБ < 5 В, вихід 5 В іде слідом за входом; SRD-05 тримається до ~2 В. ESP32 працює від АКБ 3,8 В. Іоністор не потрібен. D4: живлення від USB.
3. ESP32-S3-MINI-1U (зовнішня антена U.FL -> SMA на корпусі)
IO1 VBAT_SENSE (ADC1) IO2 CHG_DONE IO4 TAHO IO5 REMOTE IO6 MAINS_OK IO7 CHG_EN IO8 CHG_STAT IO9 LED IO10/11/12 реле K1/K2/K3 IO21 реле K4 AUX IO13-16 DIP1-4 IO17/18 резерв J7 IO0 BOOT, EN RESET; IO3/IO45/IO46 (strapping) і IO26/33-37 не використовуються.
4. USB-C: прошивка і лог (вбудований USB ESP32-S3)
5. Реле: K1 ACC, K2 START, K4 AUX (COM = VBAT), K3 контактор (сухі контакти 230 В)
Реле SRD-05VDC: котушка 5 В / 72 мА від окремого buck 5 В, ключ AO3400A, діод на котушці, світлодіод стану. Затвор притягнутий до GND (100k): поки ESP32 завантажується, реле вимкнені.
6. Входи: TAHO (LM393), REMOTE
TAHO: 22k -> два стабілітрони 5,1 В -> 10 мкФ -> 10k на GND -> фільтр 10k/10 нФ (100 мкс) -> LM393. BAV99 обмежує вхід LM393 від -0,6 до 3,9 В. Поріг VB = 22k/10k + гістерезис 100k: 0,97 / 1,18 В. Вхід у спокої на 0 В, нижче порогу: вихід HIGH. Живий дріт TAHO не можна садити на масу.
REMOTE: сухий контакт на GND, замкнено = запуск.
7. 230 В: запобіжник, варистор, AC-DC 24 В, детектор мережі (зазор >= 8 мм до низьковольтної частини)
Детектор: 3 x 47k (1206) -> оптопара з двома світлодіодами (AC). Мережа є = MAINS_OK низький. 1 мкФ згладжує провали біля нуля синусоїди. PS1: ізоляція всередині модуля, -Vout = GND плати.
8. Зарядник свинцевої АКБ (CN3767): 14,8 В заряд / 13,55 В підтримка, 1 А
Q20 вимикач живлення зарядника (Vgs = 12 В). CHG_EN: HIGH або ESP32 не працює = зарядка йде, LOW = зарядка вимкнена (прокрутка стартера, DIP2 OFF).
MPPT 150k/10k: якщо AC-DC просідає нижче ~19 В, зарядник зменшує струм. COM: 120 Ом + 220 нФ (компенсація). RCS 0,12 Ом = 1 А, Kelvin-доріжки до CSP/BAT.
9. DIP, світлодіоди, роз'єми, кріплення
DIP (замкнено = ON, внутрішні підтяжки ESP32): 1 режим: OFF = REMOTE, ON = пропала мережа 2 зарядка дозволена 3 затримка запуску 10 / 60 с 4 AUX: OFF = підігрів до пуску, ON = декомпресія під час прокрутки
H1-H4: кріплення M3 по кутах плати.
